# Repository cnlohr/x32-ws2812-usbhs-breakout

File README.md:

# 32x parallel WS 2812 Driver with High-Speed USB

This project leverages the CH32V305's USB High Speed USB interface as well as its timer-driven DMA to enable outputting to thousands of LEDs at >144 Hz!

(More documentation coming soon)

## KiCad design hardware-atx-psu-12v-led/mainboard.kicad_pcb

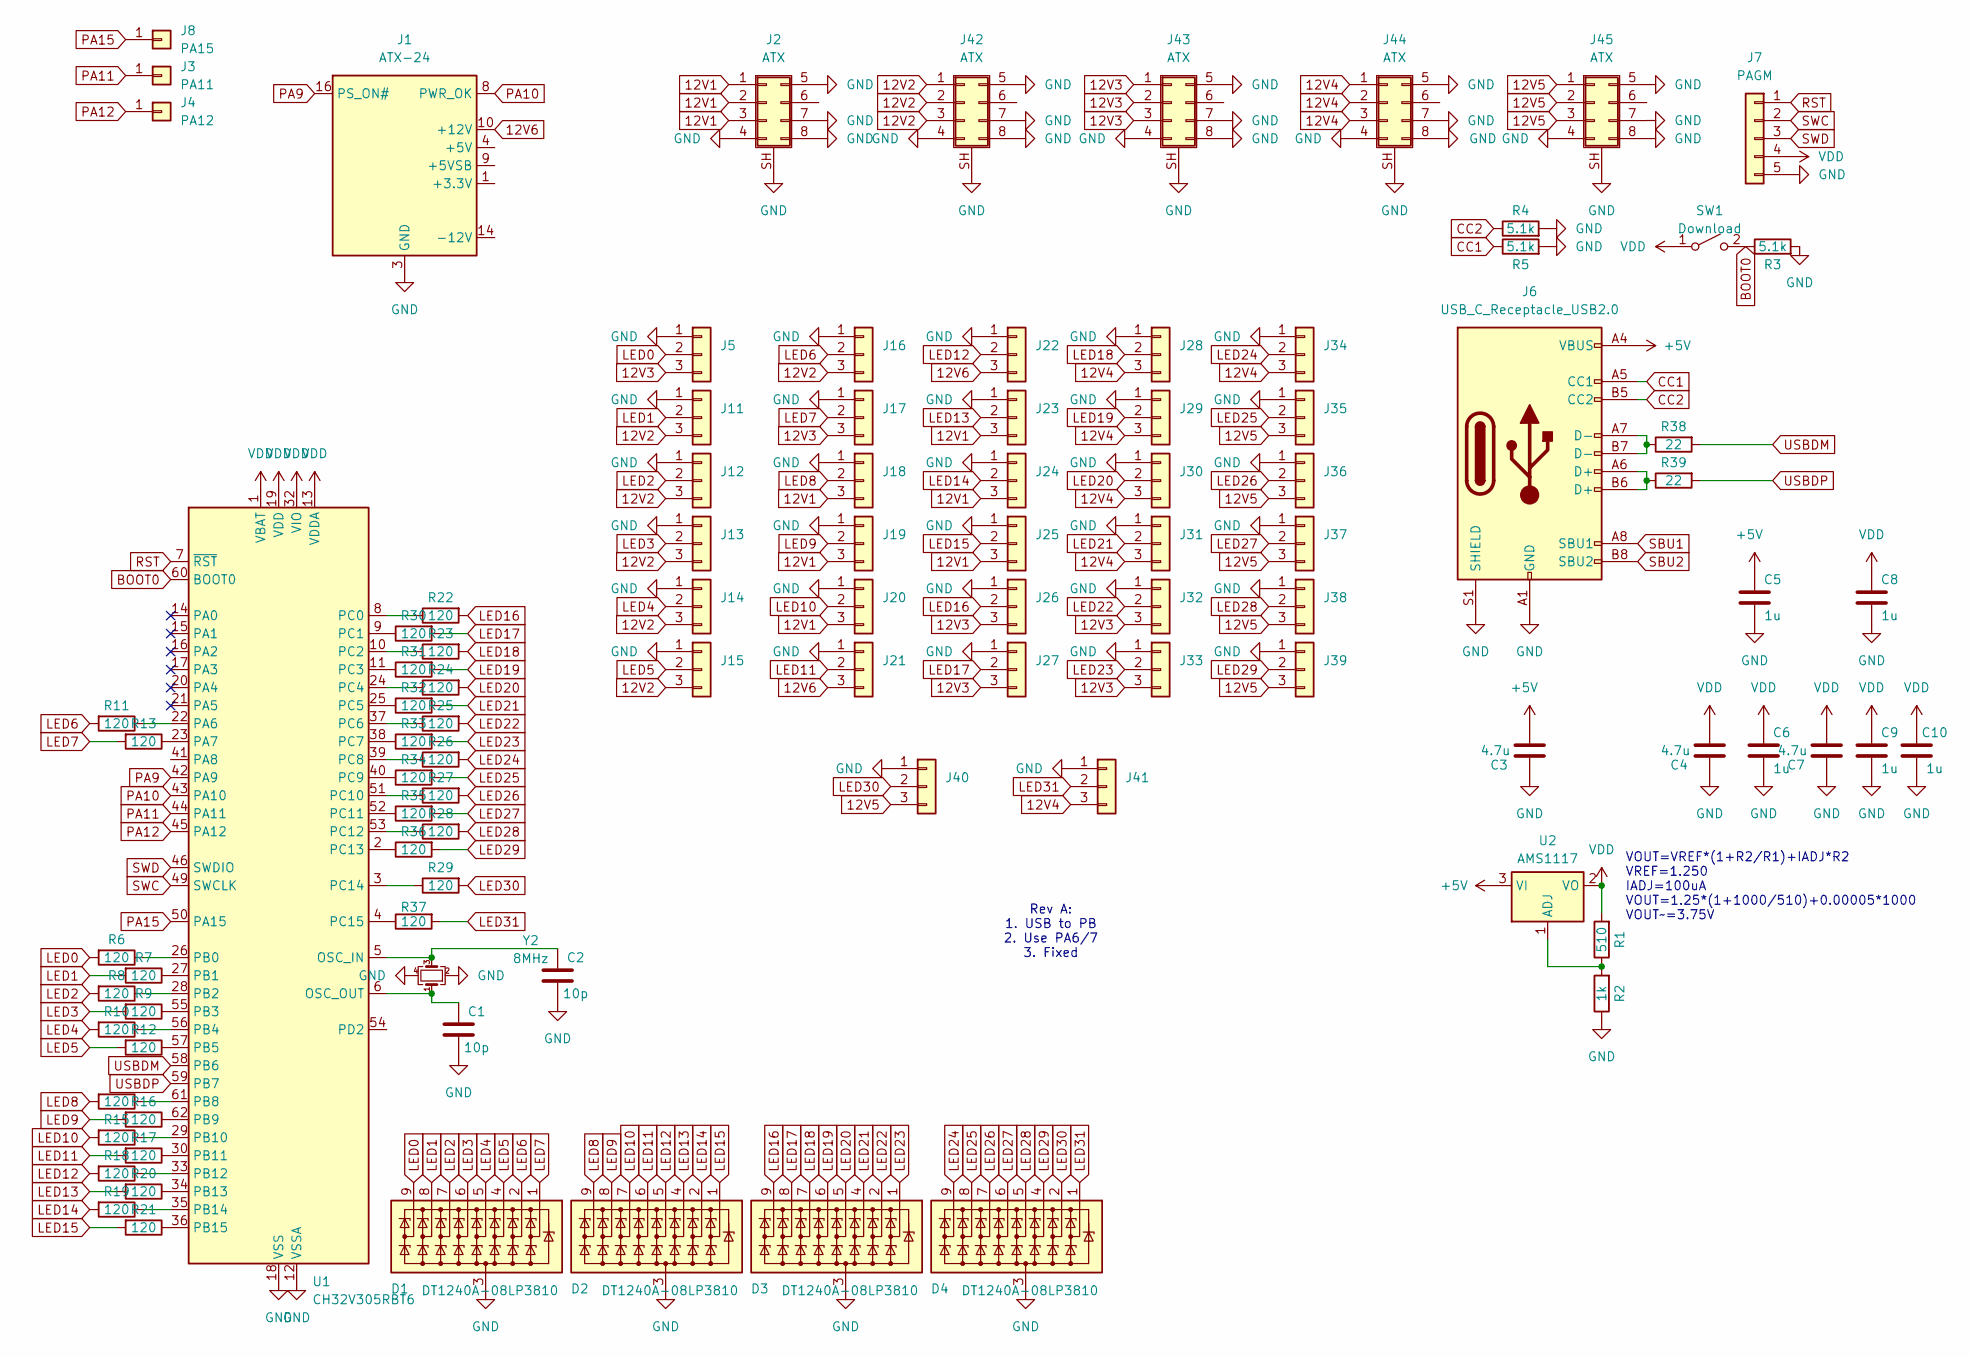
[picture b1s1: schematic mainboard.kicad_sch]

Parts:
C1, C2: 10p; R_0402_1005Metric; LCSC C32949
C3, C4, C7: 4.7u; C_0805_2012Metric; LCSC C1779
C5, C6, C8, C9, C10: 1u; R_0402_1005Metric; LCSC C52923
D1, D2, D3, D4: DT1240A-08LP3810; UDFN-9_1.0x3.8mm_P0.5mm; LCSC C526598
J1: ATX-24; Molex_Mini-Fit_Jr_5566-24A2_2x12_P4.20mm_Vertical; LCSC C114125
J2, J42, J43, J44, J45: ATX; Molex_Mini-Fit_-PCI_EXPRESS-_2x04_P4.20mm_Vertical; LCSC C2886679
J3: PA11; TestPoint_Pad_D1.0mm
J4: PA12; TestPoint_Pad_D1.0mm
J5, J11, J12, J13, J14, J15, J16, J17, J18, J19, J20, J21, J22, J23, J24, J25, J26, J27, J28, J29, J30, J31, J32, J33, J34, J35, J36, J37, J38, J39, J40, J41: LED; TerminalBlock_TE_282834-3_1x03_P2.54mm_Horizontal; LCSC C234181
J6: USB_C_Receptacle_USB2.0; USB_C_Receptacle_HRO_TYPE-C-31-M-12; LCSC C2765186
J7: PAGM; PinHeader_1x05_P2.54mm_Vertical; LCSC C32713271
J8: PA15; TestPoint_Pad_D1.0mm
R1: 510; R_0402_1005Metric; LCSC C25123
R2: 1k; R_0402_1005Metric; LCSC C11702
R3, R4, R5: 5.1k; R_0402_1005Metric; LCSC C25905
R6, R7, R8, R9, R10, R11, R12, R13, R14, R15, R16, R17, R18, R19, R20, R21, R22, R23, R24, R25, R26, R27, R28, R29, R30, R31, R32, R33, R34, R35, R36, R37: 120; R_0402_1005Metric; LCSC C25079
R38, R39: 22; R_0402_1005Metric; LCSC C25092
SW1: Download; SW_SPST_TL3342; LCSC C318884
U1: CH32V305RBT6; LQFP-64_10x10mm_P0.5mm; LCSC C5187529
U2: AMS1117; SOT-223-3_TabPin2; LCSC C110475
Y2: 8MHz; Crystal_SMD_3225-4Pin_3.2x2.5mm_HandSoldering; LCSC C367183

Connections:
12V1: J2.1, J2.2, J2.3, J18.3, J19.3, J20.3, J23.3, J24.3, J25.3
12V2: J11.3, J12.3, J13.3, J14.3, J15.3, J16.3, J42.1, J42.2, J42.3
12V3: J5.3, J17.3, J26.3, J27.3, J32.3, J33.3, J43.1, J43.2, J43.3
12V4: J28.3, J29.3, J30.3, J31.3, J34.3, J41.3, J44.1, J44.2, J44.3
12V5: J35.3, J36.3, J37.3, J38.3, J39.3, J40.3, J45.1, J45.2, J45.3
12V6: J1.10 (+12V), J1.11 (+12V), J21.3, J22.3
+5V: C3.2, C5.2, J6.A4 (VBUS), J6.A9 (VBUS), J6.B4 (VBUS), J6.B9 (VBUS), U2.3 (VI)
BOOT0: R3.1, SW1.2 (B), U1.60 (BOOT0)
CC1: J6.A5 (CC1), R5.1
CC2: J6.B5 (CC2), R4.1
GND: C1.1, C2.1, C3.1, C4.1, C5.1, C6.1, C7.1, C8.1, C9.1, C10.1, D1.3 (A), D2.3 (A), D3.3 (A), D4.3 (A), J1.3 (GND), J1.5 (GND), J1.7 (GND), J1.15 (GND), J1.17 (GND), J1.18 (GND), J1.19 (GND), J1.24 (GND), J2.4, J2.5, J2.7, J2.8, J2.SH (Shield), J5.1, J6.A1 (GND), J6.A12 (GND), J6.B1 (GND), J6.B12 (GND), J6.S1 (SHIELD), J7.5, J11.1, J12.1, J13.1, J14.1, J15.1, J16.1, J17.1, J18.1, J19.1, J20.1, J21.1, J22.1, J23.1, J24.1, J25.1, J26.1, J27.1, J28.1, J29.1, J30.1, J31.1, J32.1, J33.1, J34.1, J35.1, J36.1, J37.1, J38.1, J39.1, J40.1, J41.1, J42.4, J42.5, J42.7, J42.8, J42.SH (Shield), J43.4, J43.5, J43.7, J43.8, J43.SH (Shield), J44.4, J44.5, J44.7, J44.8, J44.SH (Shield), J45.4, J45.5, J45.8, J45.SH (Shield), R2.1, R3.2, R4.2, R5.2, U1.12 (VSSA), U1.18 (VSS), U1.31 (VSS), U1.47 (VSS), U1.63 (VSS), Y2.2, Y2.4
LED0: D1.9 (K8), J5.2, R6.2
LED1: D1.8 (K7), J11.2, R7.2
LED2: D1.7 (K6), J12.2, R8.2
LED3: D1.6 (K5), J13.2, R9.2
LED4: D1.5 (K4), J14.2, R10.2
LED5: D1.4 (K3), J15.2, R12.2
LED6: D1.2 (K2), J16.2, R11.2
LED7: D1.1 (K1), J17.2, R13.2
LED8: D2.9 (K8), J18.2, R14.2
LED9: D2.8 (K7), J19.2, R16.2
LED10: D2.7 (K6), J20.2, R15.2
LED11: D2.6 (K5), J21.2, R17.2
LED12: D2.5 (K4), J22.2, R18.2
LED13: D2.4 (K3), J23.2, R20.2
LED14: D2.2 (K2), J24.2, R19.2
LED15: D2.1 (K1), J25.2, R21.2
LED16: D3.9 (K8), J26.2, R22.2
LED17: D3.8 (K7), J27.2, R30.2
LED18: D3.7 (K6), J28.2, R23.2
LED19: D3.6 (K5), J29.2, R31.2
LED20: D3.5 (K4), J30.2, R24.2
LED21: D3.4 (K3), J31.2, R32.2
LED22: D3.2 (K2), J32.2, R25.2
LED23: D3.1 (K1), J33.2, R33.2
LED24: D4.9 (K8), J34.2, R26.2
LED25: D4.8 (K7), J35.2, R34.2
LED26: D4.7 (K6), J36.2, R27.2
LED27: D4.6 (K5), J37.2, R35.2
LED28: D4.5 (K4), J38.2, R28.2
LED29: D4.4 (K3), J39.2, R36.2
LED30: D4.2 (K2), J40.2, R29.2
LED31: D4.1 (K1), J41.2, R37.2
unnamed: J1.1 (+3.3V), J1.2 (+3.3V), J1.12 (+3.3V), J1.13 (+3.3V)
unnamed: J1.4 (+5V), J1.6 (+5V), J1.21 (+5V), J1.22 (+5V), J1.23 (+5V)
unnamed: J6.A6 (D+), J6.B6 (D+), R39.1
unnamed: J6.A7 (D-), J6.B7 (D-), R38.1
unnamed: C2.2, U1.5 (OSC_IN), Y2.3
unnamed: C1.2, U1.6 (OSC_OUT), Y2.1
unnamed: R11.1, U1.22 (PA6)
unnamed: R13.1, U1.23 (PA7)
unnamed: R6.1, U1.26 (PB0)
unnamed: R7.1, U1.27 (PB1)
unnamed: R8.1, U1.28 (PB2)
unnamed: R9.1, U1.55 (PB3)
unnamed: R10.1, U1.56 (PB4)
unnamed: R12.1, U1.57 (PB5)
unnamed: R14.1, U1.61 (PB8)
unnamed: R16.1, U1.62 (PB9)
unnamed: R15.1, U1.29 (PB10)
unnamed: R17.1, U1.30 (PB11)
unnamed: R18.1, U1.33 (PB12)
unnamed: R20.1, U1.34 (PB13)
unnamed: R19.1, U1.35 (PB14)
unnamed: R21.1, U1.36 (PB15)
unnamed: R22.1, U1.8 (PC0)
unnamed: R30.1, U1.9 (PC1)
unnamed: R23.1, U1.10 (PC2)
unnamed: R31.1, U1.11 (PC3)
unnamed: R24.1, U1.24 (PC4)
unnamed: R32.1, U1.25 (PC5)
unnamed: R25.1, U1.37 (PC6)
unnamed: R33.1, U1.38 (PC7)
unnamed: R26.1, U1.39 (PC8)
unnamed: R34.1, U1.40 (PC9)
unnamed: R27.1, U1.51 (PC10)
unnamed: R35.1, U1.52 (PC11)
unnamed: R28.1, U1.53 (PC12)
unnamed: R36.1, U1.2 (PC13)
unnamed: R29.1, U1.3 (PC14)
unnamed: R37.1, U1.4 (PC15)
unnamed: R1.1, R2.2, U2.1 (ADJ)
PA9: J1.16 (PS_ON#), U1.42 (PA9)
PA10: J1.8 (PWR_OK), U1.43 (PA10)
PA11: J3.1, U1.44 (PA11)
PA12: J4.1, U1.45 (PA12)
PA15: J8.1, U1.50 (PA15)
RST: J7.1, U1.7 (~RST)
SBU1: J6.A8 (SBU1)
SBU2: J6.B8 (SBU2)
SWC: J7.2, U1.49 (SWCLK)
SWD: J7.3, U1.46 (SWDIO)
USBDM: R38.2, U1.58 (PB6)
USBDP: R39.2, U1.59 (PB7)
VDD: C4.2, C6.2, C7.2, C8.2, C9.2, C10.2, J7.4, R1.2, SW1.1 (A), U1.1 (VBAT), U1.13 (VDDA), U1.19 (VDD), U1.32 (VIO), U1.48 (VDD), U1.64 (VIO), U2.2 (VO)

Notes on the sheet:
Rev A: 1. USB to PB 2. Use PA6/7 3. Fixed
VOUT=VREF*(1+R2/R1)+IADJ*R2 VREF=1.250 IADJ=100uA VOUT=1.25*(1+1000/510)+0.00005*1000 VOUT~=3.75V

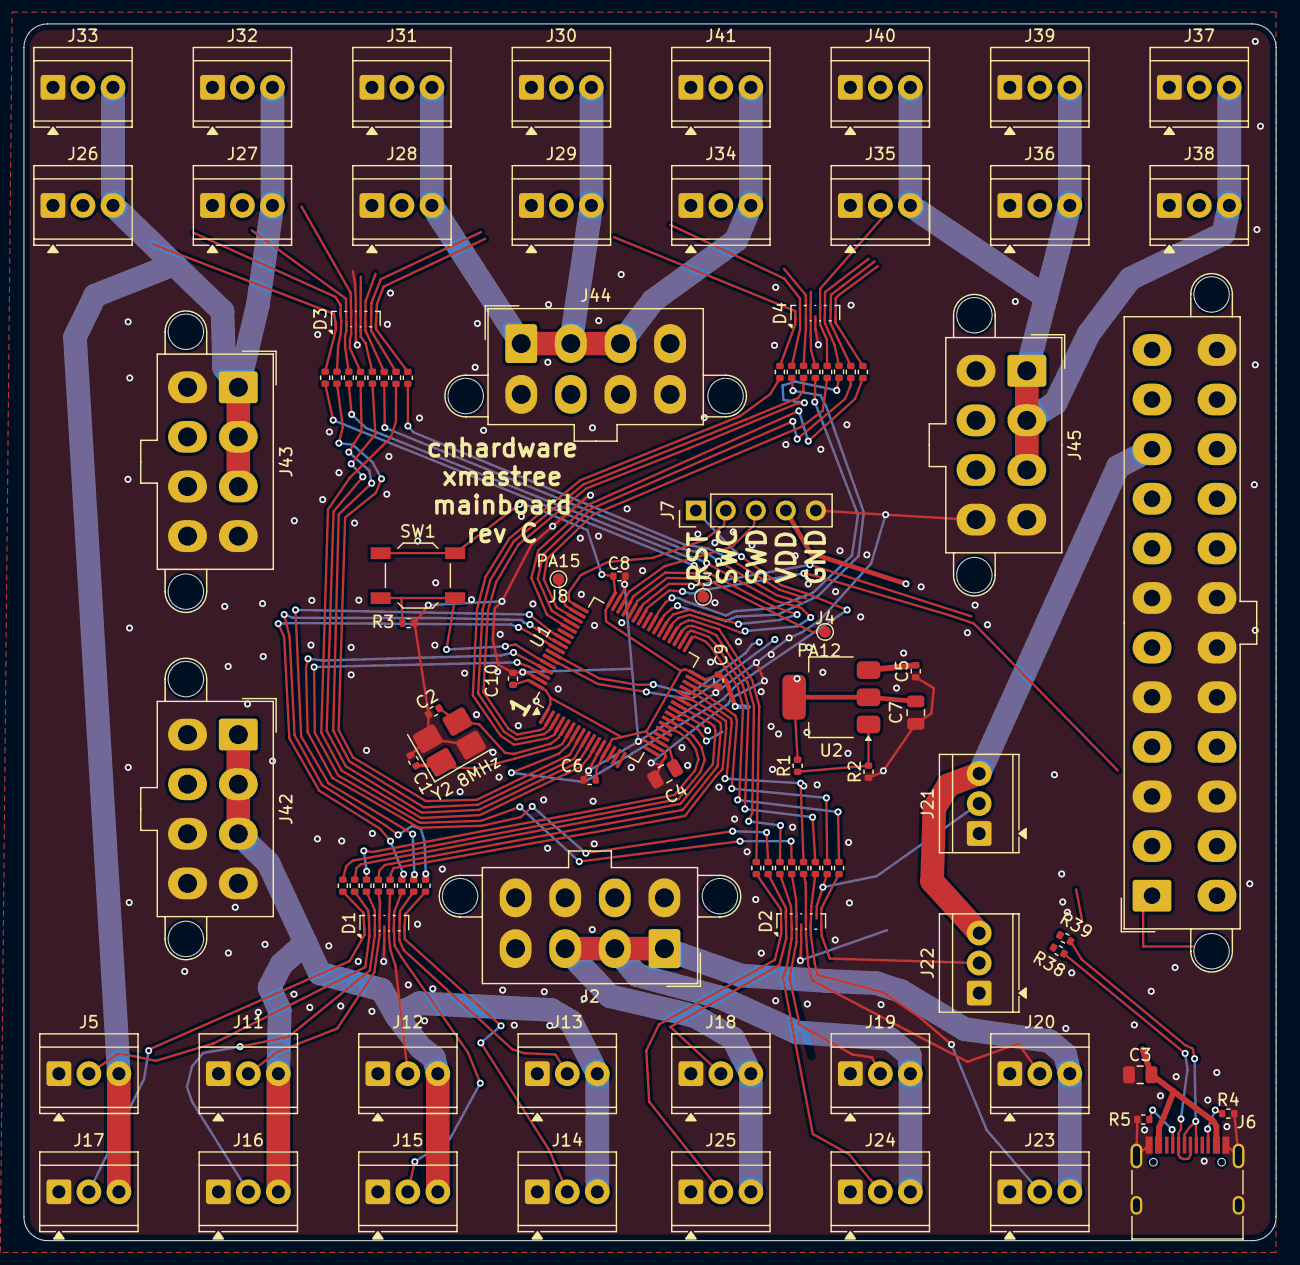
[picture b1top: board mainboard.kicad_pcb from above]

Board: 2 copper layers, 106.0 x 103.0 mm, 100 parts (0 on the bottom side), 93 nets.

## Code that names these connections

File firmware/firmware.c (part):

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	funGpioInitAll();

	funPinMode( PA3, GPIO_CFGLR_OUT_10Mhz_PP ); // Old PSU on signal
	funPinMode( PA9, GPIO_CFGLR_OUT_10Mhz_PP ); // New PSU on signal

    Delay_Ms(200);

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	RCC->APB2PCENR = RCC_APB2Periph_TIM1 | RCC_APB2Periph_TIM10 | RCC_APB2Periph_AFIO  | RCC_APB2Periph_GPIOA | RCC_APB2Periph_GPIOB | RCC_APB2Periph_GPIOC | RCC_APB2Periph_GPIOD | RCC_APB2Periph_GPIOE;
	RCC->APB1PCENR |= RCC_APB1Periph_TIM2;

	funPinMode( PA9, GPIO_CFGLR_OUT_50Mhz_PP );
	funDigitalWrite( PA9, 0);

	funPinMode( PA6, GPIO_CFGLR_OUT_10Mhz_PP );
	funPinMode( PA7, GPIO_CFGLR_OUT_10Mhz_PP );

	GPIOC->CFGLR = 0x11111111; // All output.  All 10MHz
	GPIOC->CFGHR = 0x11111111; // All output.  All 10MHz

	GPIOB->CFGHR = 0x11111111; // All output.  All 10MHz
	GPIOB->CFGLR = 0xbb111111; // All output.  All 10MHz  (Except for USB pins, PB6, PB7)

	// DMA2 = T1CH1
	DMA1_Channel2->CNTR = 1;
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
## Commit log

2025-12-08 Add initial commit
2025-12-08 Add new demo and reorganize files
2025-12-09 Update to a test we can use
2025-12-09 Further tweaks
2025-12-09 getting close for tonight
2025-12-09 Fix for port b
2025-12-09 Further cleanup
2025-12-09 Add double-demo
2025-12-09 Tweaked per these LEDs
2025-12-09 Add readme and move hardware
2025-12-10 Trying out winusb descriptor
2025-12-10 Driverify tool
2025-12-10 Get close to adding HPD mode
2025-12-10 Add note about device add
2025-12-10 Update with hpd but it doesn't quite work
2025-12-10 Fixup with hotplug
2025-12-10 Remove superfurolous debugging.
2025-12-19 Add revB
2025-12-19 Fix PB14, PB15 outputs
2025-12-19 cleanup firmware
2025-12-26 Tweak holes on power connector
2026-02-06 Update with more spacing around connectors
2026-02-06 bump design
